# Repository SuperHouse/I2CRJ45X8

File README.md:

I2C to RJ45 Breakout (8 Port)
=============================
Copyright 2019-2021 SuperHouse Automation Pty Ltd  www.superhouse.tv  

8 RJ45 sockets connected to 32 I/O channels via I2C addressable
I/O controllers. Intended for use in building a home automation light
switch controller for connection to SuperHouse light switches.

Features:

 * 8 x RJ45 sockets for connection to light switches over Cat-5
 * I2C interface with interrupt output

This project has different versions:

 * 8-port version: https://github.com/superhouse/i2crj45x8
 * 16-port version: https://github.com/superhouse/i2crj45x16
 * 24-port version: https://github.com/superhouse/i2crj45x24
 * 24-port version with passthrough: https://github.com/superhouse/i2crj45x24pt

More information:

  http://www.superhouse.tv/i2crj45x8

INSTALLATION
------------
The design is saved as an EAGLE project. EAGLE PCB design software is
available from www.cadsoftusa.com free for non-commercial use. To use
this project download it and place the directory containing these files
into the "eagle" directory on your computer. Then open EAGLE and
navigate to the project.

CREDITS
-------
Designed by Jonathan Oxer jon@oxer.com.au

DISTRIBUTION
------------
The specific terms of distribution of this project are governed by the
license referenced below.

LICENSE
-------
Licensed under the TAPR Open Hardware License (www.tapr.org/OHL).
The "license" folder within this repository also contains a copy of
this license in plain text format.

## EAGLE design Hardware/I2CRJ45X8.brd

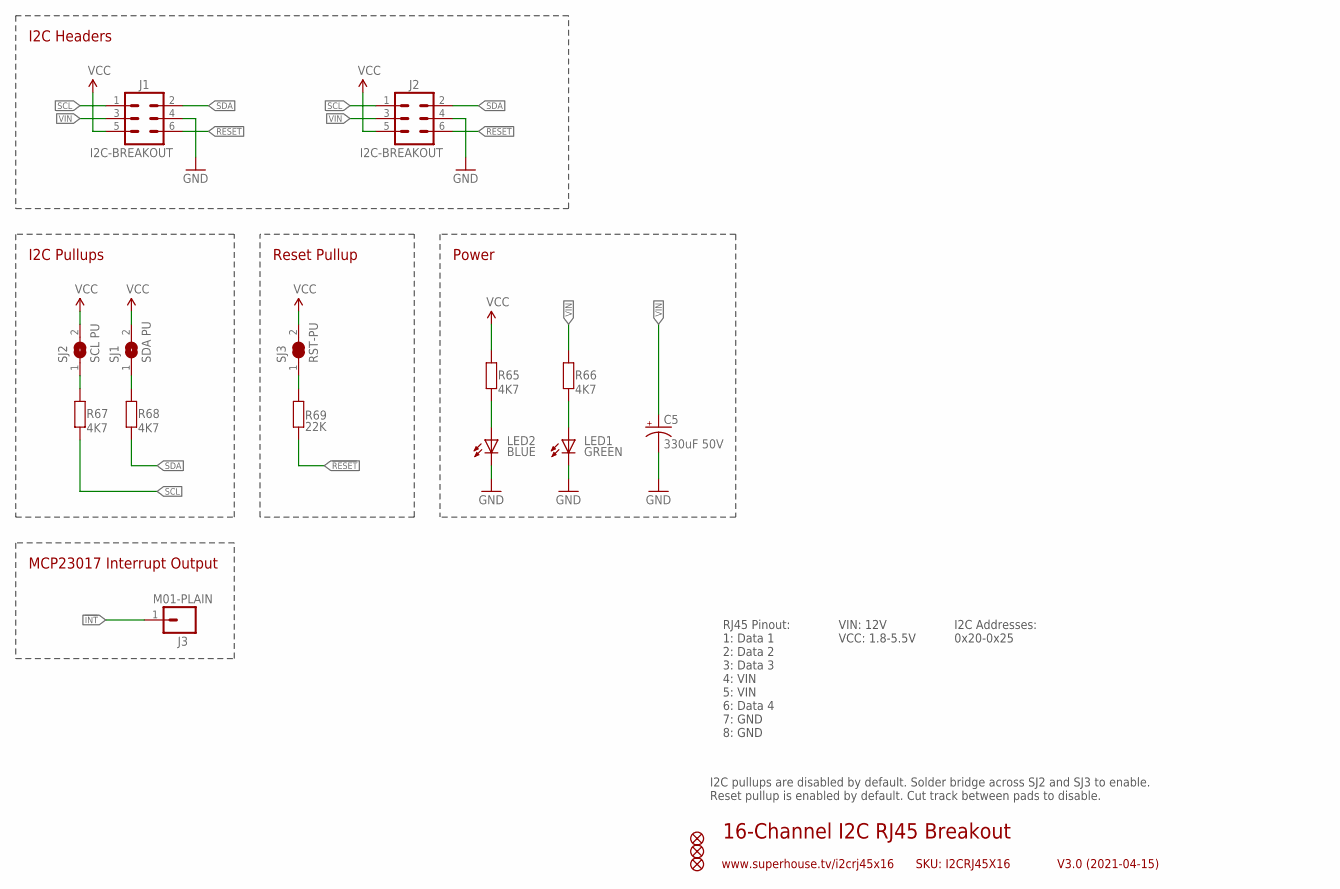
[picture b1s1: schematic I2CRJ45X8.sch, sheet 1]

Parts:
C5: 330uF 50V; PANASONIC_G
FID1, FID2, FID3: FIDUCIAL1X2.5; FIDUCIAL-1X2.5
J1, J2: I2C-BREAKOUT; 2X03-SHROUDED
J3: M01-PLAIN; 1X01
LED1: GREEN; LED-0603
LED2: BLUE; LED-0603
R65, R66, R67, R68: 4K7; R0603
R69: 22K; R0603
SJ1: SDA PU; SJ
SJ2: SCL PU; SJ
SJ3: RST-PU; SJC

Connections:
!INT: J3.1; also elsewhere on the board
!RESET: J1.6, J2.6, R69.1; also elsewhere on the board
GND: C5.-, J1.4, J2.4, LED1.C, LED2.C; also elsewhere on the board
unnamed: R67.2, SJ2.1
unnamed: R68.2, SJ1.1
unnamed: R69.2, SJ3.1
unnamed: LED2.A, R65.1
unnamed: LED1.A, R66.1
SCL: J1.1, J2.1, R67.1; also elsewhere on the board
SDA: J1.2, J2.2, R68.1; also elsewhere on the board
VCC: J1.5, J2.5, R65.2, SJ1.2, SJ2.2, SJ3.2; also elsewhere on the board
VIN: C5.+, J1.3, J2.3, R66.2; also elsewhere on the board

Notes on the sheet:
16-Channel I2C RJ45 Breakout
V3.0 (2021-04-15)
www.superhouse.tv/i2crj45x16
SKU: I2CRJ45X16
RJ45 Pinout: 1: Data 1 2: Data 2 3: Data 3 4: VIN 5: VIN 6: Data 4 7: GND 8: GND
VIN: 12V VCC: 1.8-5.5V
I2C Addresses: 0x20-0x25
I2C Headers
MCP23017 Interrupt Output
I2C Pullups
I2C pullups are disabled by default. Solder bridge across SJ2 and SJ3 to enable. Reset pullup is enabled by default. Cut track between pads to disable.
Power
Reset Pullup

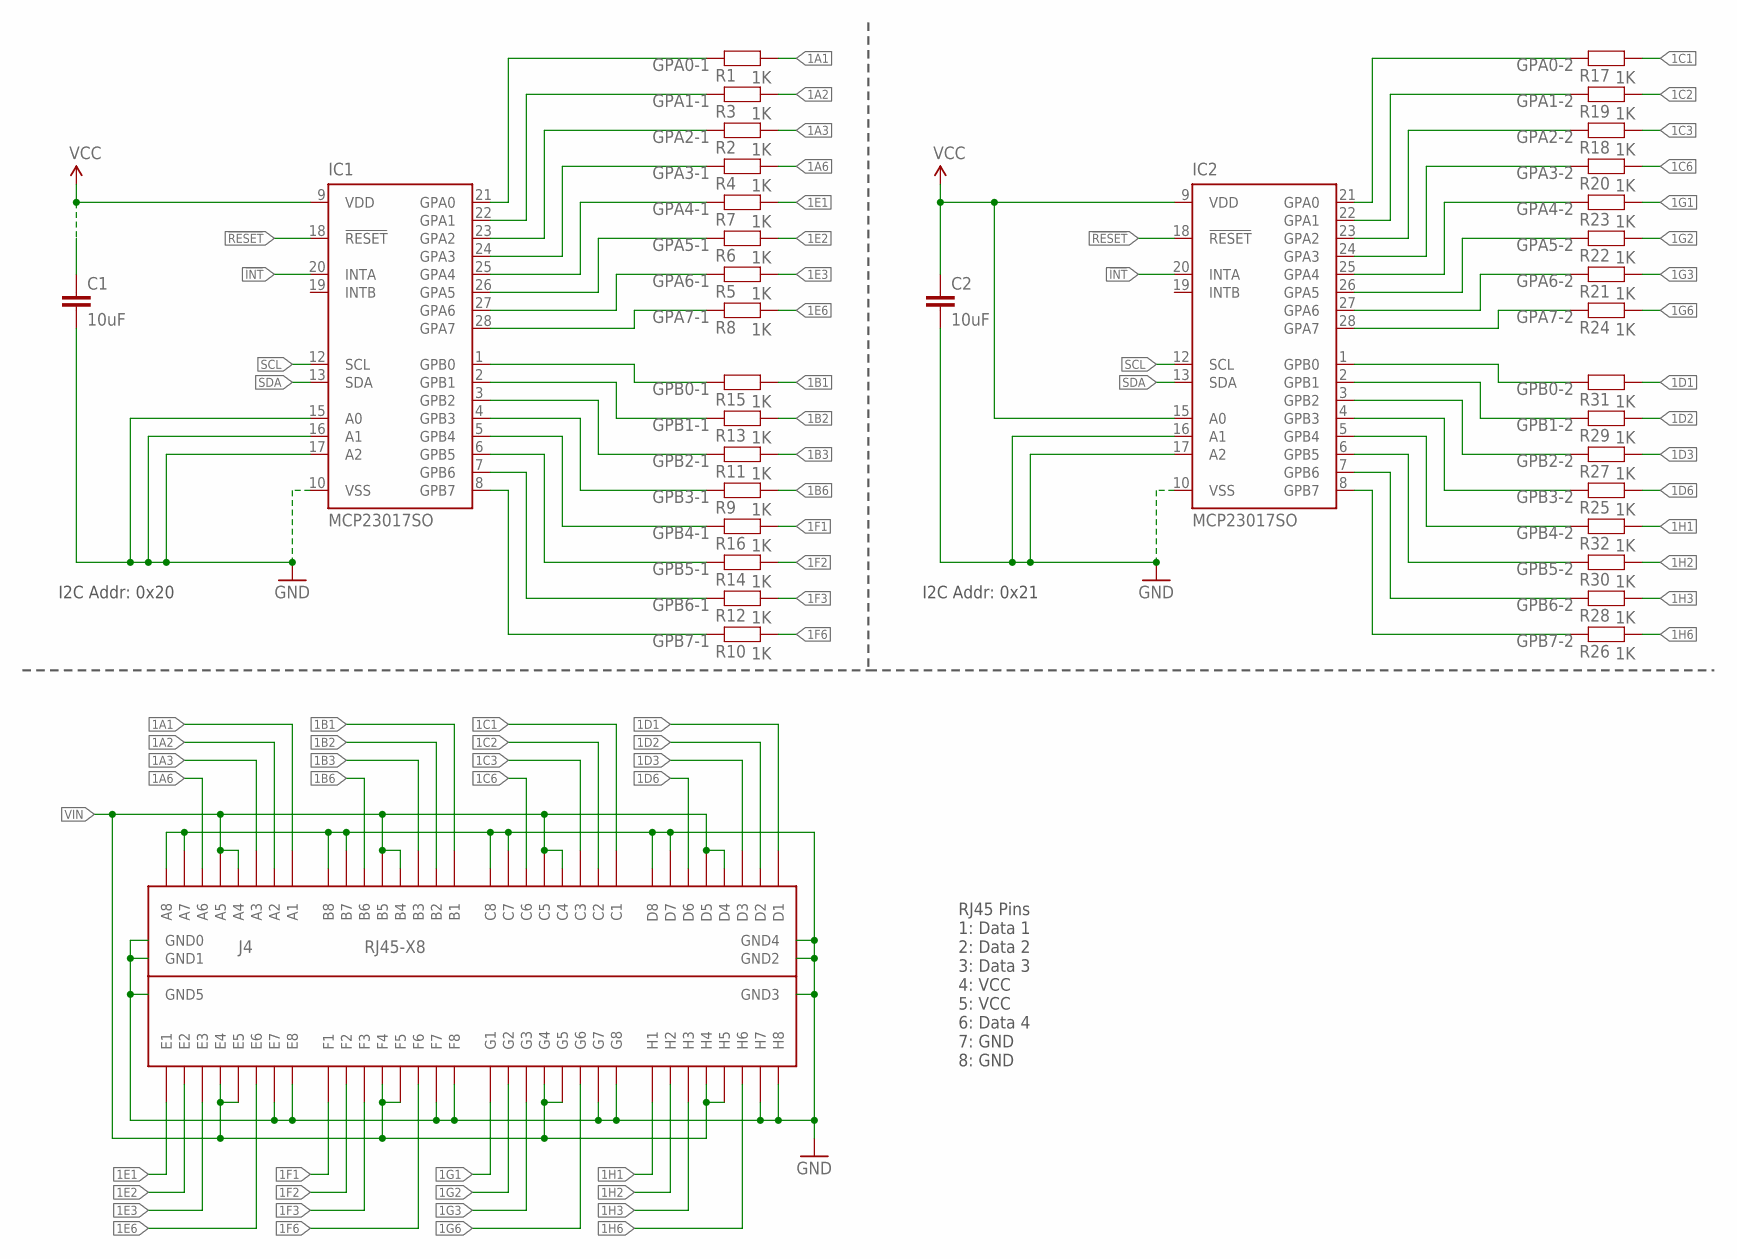
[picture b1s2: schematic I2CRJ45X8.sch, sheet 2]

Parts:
C1, C2: 10uF; C0805
IC1, IC2: MCP23017SO; SO28W
J4: RJ45-X8; RJ45-2X4
R1, R2, R3, R4, R5, R6, R7, R8, R9, R10, R11, R12, R13, R14, R15, R16, R17, R18, R19, R20, R21, R22, R23, R24, R25, R26, R27, R28, R29, R30, R31, R32: 1K; R0603

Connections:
1A1: J4.A1, R1.2
1A2: J4.A2, R3.2
1A3: J4.A3, R2.2
1A6: J4.A6, R4.2
1B1: J4.B1, R15.2
1B2: J4.B2, R13.2
1B3: J4.B3, R11.2
1B6: J4.B6, R9.2
1C1: J4.C1, R17.2
1C2: J4.C2, R19.2
1C3: J4.C3, R18.2
1C6: J4.C6, R20.2
1D1: J4.D1, R31.2
1D2: J4.D2, R29.2
1D3: J4.D3, R27.2
1D6: J4.D6, R25.2
1E1: J4.E1, R7.2
1E2: J4.E2, R6.2
1E3: J4.E3, R5.2
1E6: J4.E6, R8.2
1F1: J4.F1, R16.2
1F2: J4.F2, R14.2
1F3: J4.F3, R12.2
1F6: J4.F6, R10.2
1G1: J4.G1, R23.2
1G2: J4.G2, R22.2
1G3: J4.G3, R21.2
1G6: J4.G6, R24.2
1H1: J4.H1, R32.2
1H2: J4.H2, R30.2
1H3: J4.H3, R28.2
1H6: J4.H6, R26.2
!INT: IC1.20 (INTA), IC2.20 (INTA); also elsewhere on the board
!RESET: IC1.18 (!RESET), IC2.18 (!RESET); also elsewhere on the board
GND: C1.2, C2.2, IC1.10 (VSS), IC1.15 (A0), IC1.16 (A1), IC1.17 (A2), IC2.10 (VSS), IC2.16 (A1), IC2.17 (A2), J4.A7, J4.A8, J4.B7, J4.B8, J4.C7, J4.C8, J4.D7, J4.D8, J4.E7, J4.E8, J4.F7, J4.F8, J4.G7, J4.G8, J4.GND0, J4.GND1, J4.GND2, J4.GND3, J4.GND4, J4.GND5, J4.H7, J4.H8; also elsewhere on the board
GPA0-1: IC1.21 (GPA0), R1.1
GPA0-2: IC2.21 (GPA0), R17.1
GPA1-1: IC1.22 (GPA1), R3.1
GPA1-2: IC2.22 (GPA1), R19.1
GPA2-1: IC1.23 (GPA2), R2.1
GPA2-2: IC2.23 (GPA2), R18.1
GPA3-1: IC1.24 (GPA3), R4.1
GPA3-2: IC2.24 (GPA3), R20.1
GPA4-1: IC1.25 (GPA4), R7.1
GPA4-2: IC2.25 (GPA4), R23.1
GPA5-1: IC1.26 (GPA5), R6.1
GPA5-2: IC2.26 (GPA5), R22.1
GPA6-1: IC1.27 (GPA6), R5.1
GPA6-2: IC2.27 (GPA6), R21.1
GPA7-1: IC1.28 (GPA7), R8.1
GPA7-2: IC2.28 (GPA7), R24.1
GPB0-1: IC1.1 (GPB0), R15.1
GPB0-2: IC2.1 (GPB0), R31.1
GPB1-1: IC1.2 (GPB1), R13.1
GPB1-2: IC2.2 (GPB1), R29.1
GPB2-1: IC1.3 (GPB2), R11.1
GPB2-2: IC2.3 (GPB2), R27.1
GPB3-1: IC1.4 (GPB3), R9.1
GPB3-2: IC2.4 (GPB3), R25.1
GPB4-1: IC1.5 (GPB4), R16.1
GPB4-2: IC2.5 (GPB4), R32.1
GPB5-1: IC1.6 (GPB5), R14.1
GPB5-2: IC2.6 (GPB5), R30.1
GPB6-1: IC1.7 (GPB6), R12.1
GPB6-2: IC2.7 (GPB6), R28.1
GPB7-1: IC1.8 (GPB7), R10.1
GPB7-2: IC2.8 (GPB7), R26.1
SCL: IC1.12 (SCL), IC2.12 (SCL); also elsewhere on the board
SDA: IC1.13 (SDA), IC2.13 (SDA); also elsewhere on the board
VCC: C1.1, C2.1, IC1.9 (VDD), IC2.9 (VDD), IC2.15 (A0); also elsewhere on the board
VIN: J4.A4, J4.A5, J4.B4, J4.B5, J4.C4, J4.C5, J4.D4, J4.D5, J4.E4, J4.E5, J4.F4, J4.F5, J4.G4, J4.G5, J4.H4, J4.H5; also elsewhere on the board

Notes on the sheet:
RJ45 Pins 1: Data 1 2: Data 2 3: Data 3 4: VCC 5: VCC 6: Data 4 7: GND 8: GND
I2C Addr: 0x20
I2C Addr: 0x21

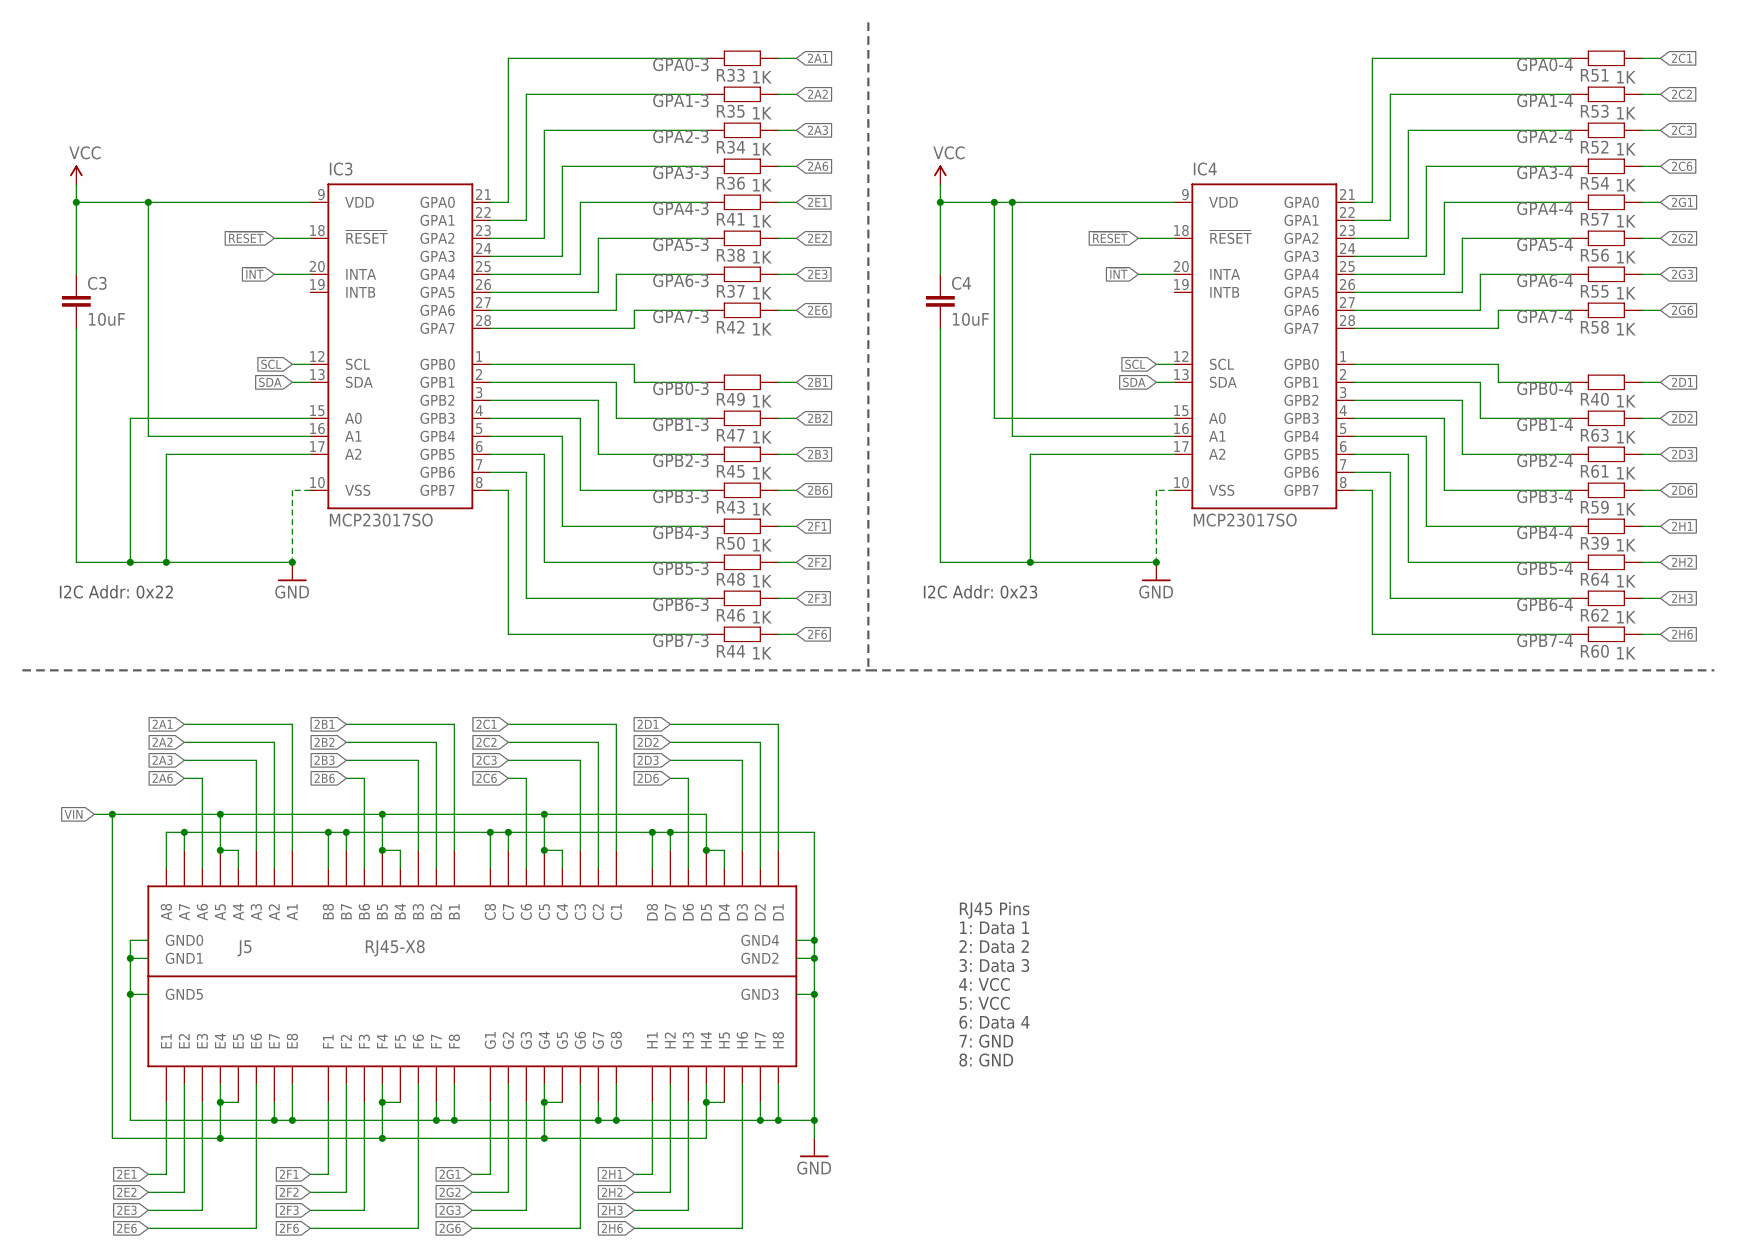
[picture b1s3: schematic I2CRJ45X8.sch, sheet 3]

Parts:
C3, C4: 10uF; C0805
IC3, IC4: MCP23017SO; SO28W
J5: RJ45-X8; RJ45-2X4
R33, R34, R35, R36, R37, R38, R39, R40, R41, R42, R43, R44, R45, R46, R47, R48, R49, R50, R51, R52, R53, R54, R55, R56, R57, R58, R59, R60, R61, R62, R63, R64: 1K; R0603

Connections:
2A1: J5.A1, R33.2
2A2: J5.A2, R35.2
2A3: J5.A3, R34.2
2A6: J5.A6, R36.2
2B1: J5.B1, R49.2
2B2: J5.B2, R47.2
2B3: J5.B3, R45.2
2B6: J5.B6, R43.2
2C1: J5.C1, R51.2
2C2: J5.C2, R53.2
2C3: J5.C3, R52.2
2C6: J5.C6, R54.2
2D1: J5.D1, R40.2
2D2: J5.D2, R63.2
2D3: J5.D3, R61.2
2D6: J5.D6, R59.2
2E1: J5.E1, R41.2
2E2: J5.E2, R38.2
2E3: J5.E3, R37.2
2E6: J5.E6, R42.2
2F1: J5.F1, R50.2
2F2: J5.F2, R48.2
2F3: J5.F3, R46.2
2F6: J5.F6, R44.2
2G1: J5.G1, R57.2
2G2: J5.G2, R56.2
2G3: J5.G3, R55.2
2G6: J5.G6, R58.2
2H1: J5.H1, R39.2
2H2: J5.H2, R64.2
2H3: J5.H3, R62.2
2H6: J5.H6, R60.2
!INT: IC3.20 (INTA), IC4.20 (INTA); also elsewhere on the board
!RESET: IC3.18 (!RESET), IC4.18 (!RESET); also elsewhere on the board
GND: C3.2, C4.2, IC3.10 (VSS), IC3.15 (A0), IC3.17 (A2), IC4.10 (VSS), IC4.17 (A2), J5.A7, J5.A8, J5.B7, J5.B8, J5.C7, J5.C8, J5.D7, J5.D8, J5.E7, J5.E8, J5.F7, J5.F8, J5.G7, J5.G8, J5.GND0, J5.GND1, J5.GND2, J5.GND3, J5.GND4, J5.GND5, J5.H7, J5.H8; also elsewhere on the board
GPA0-3: IC3.21 (GPA0), R33.1
GPA0-4: IC4.21 (GPA0), R51.1
GPA1-3: IC3.22 (GPA1), R35.1
GPA1-4: IC4.22 (GPA1), R53.1
GPA2-3: IC3.23 (GPA2), R34.1
GPA2-4: IC4.23 (GPA2), R52.1
GPA3-3: IC3.24 (GPA3), R36.1
GPA3-4: IC4.24 (GPA3), R54.1
GPA4-3: IC3.25 (GPA4), R41.1
GPA4-4: IC4.25 (GPA4), R57.1
GPA5-3: IC3.26 (GPA5), R38.1
GPA5-4: IC4.26 (GPA5), R56.1
GPA6-3: IC3.27 (GPA6), R37.1
GPA6-4: IC4.27 (GPA6), R55.1
GPA7-3: IC3.28 (GPA7), R42.1
GPA7-4: IC4.28 (GPA7), R58.1
GPB0-3: IC3.1 (GPB0), R49.1
GPB0-4: IC4.1 (GPB0), R40.1
GPB1-3: IC3.2 (GPB1), R47.1
GPB1-4: IC4.2 (GPB1), R63.1
GPB2-3: IC3.3 (GPB2), R45.1
GPB2-4: IC4.3 (GPB2), R61.1
GPB3-3: IC3.4 (GPB3), R43.1
GPB3-4: IC4.4 (GPB3), R59.1
GPB4-3: IC3.5 (GPB4), R50.1
GPB4-4: IC4.5 (GPB4), R39.1
GPB5-3: IC3.6 (GPB5), R48.1
GPB5-4: IC4.6 (GPB5), R64.1
GPB6-3: IC3.7 (GPB6), R46.1
GPB6-4: IC4.7 (GPB6), R62.1
GPB7-3: IC3.8 (GPB7), R44.1
GPB7-4: IC4.8 (GPB7), R60.1
SCL: IC3.12 (SCL), IC4.12 (SCL); also elsewhere on the board
SDA: IC3.13 (SDA), IC4.13 (SDA); also elsewhere on the board
VCC: C3.1, C4.1, IC3.9 (VDD), IC3.16 (A1), IC4.9 (VDD), IC4.15 (A0), IC4.16 (A1); also elsewhere on the board
VIN: J5.A4, J5.A5, J5.B4, J5.B5, J5.C4, J5.C5, J5.D4, J5.D5, J5.E4, J5.E5, J5.F4, J5.F5, J5.G4, J5.G5, J5.H4, J5.H5; also elsewhere on the board

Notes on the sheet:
RJ45 Pins 1: Data 1 2: Data 2 3: Data 3 4: VCC 5: VCC 6: Data 4 7: GND 8: GND
I2C Addr: 0x22
I2C Addr: 0x23

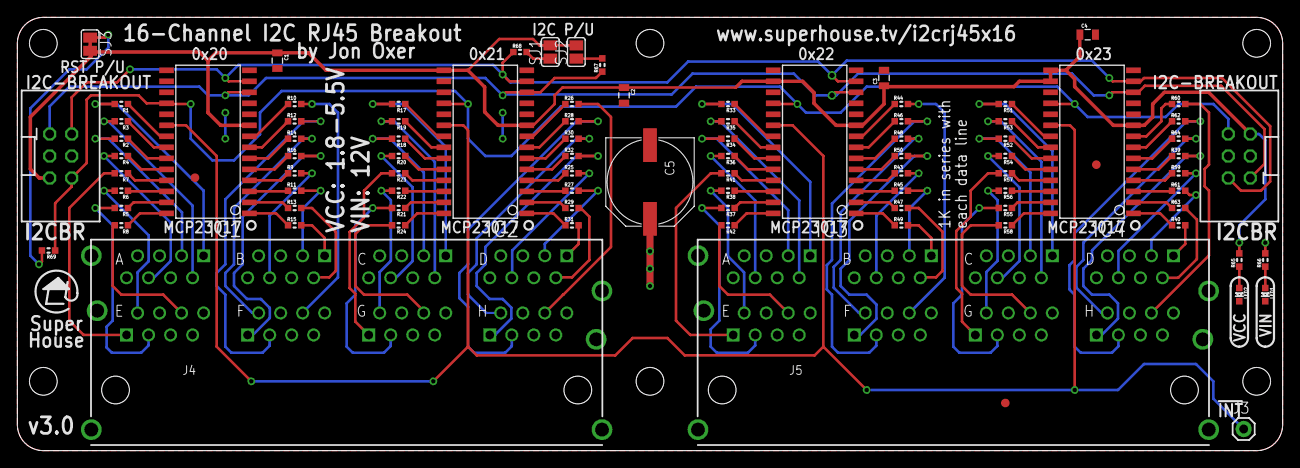
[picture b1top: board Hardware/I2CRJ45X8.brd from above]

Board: 2 copper layers, 146.0 x 50.0 mm, 91 parts (0 on the bottom side), 140 nets.

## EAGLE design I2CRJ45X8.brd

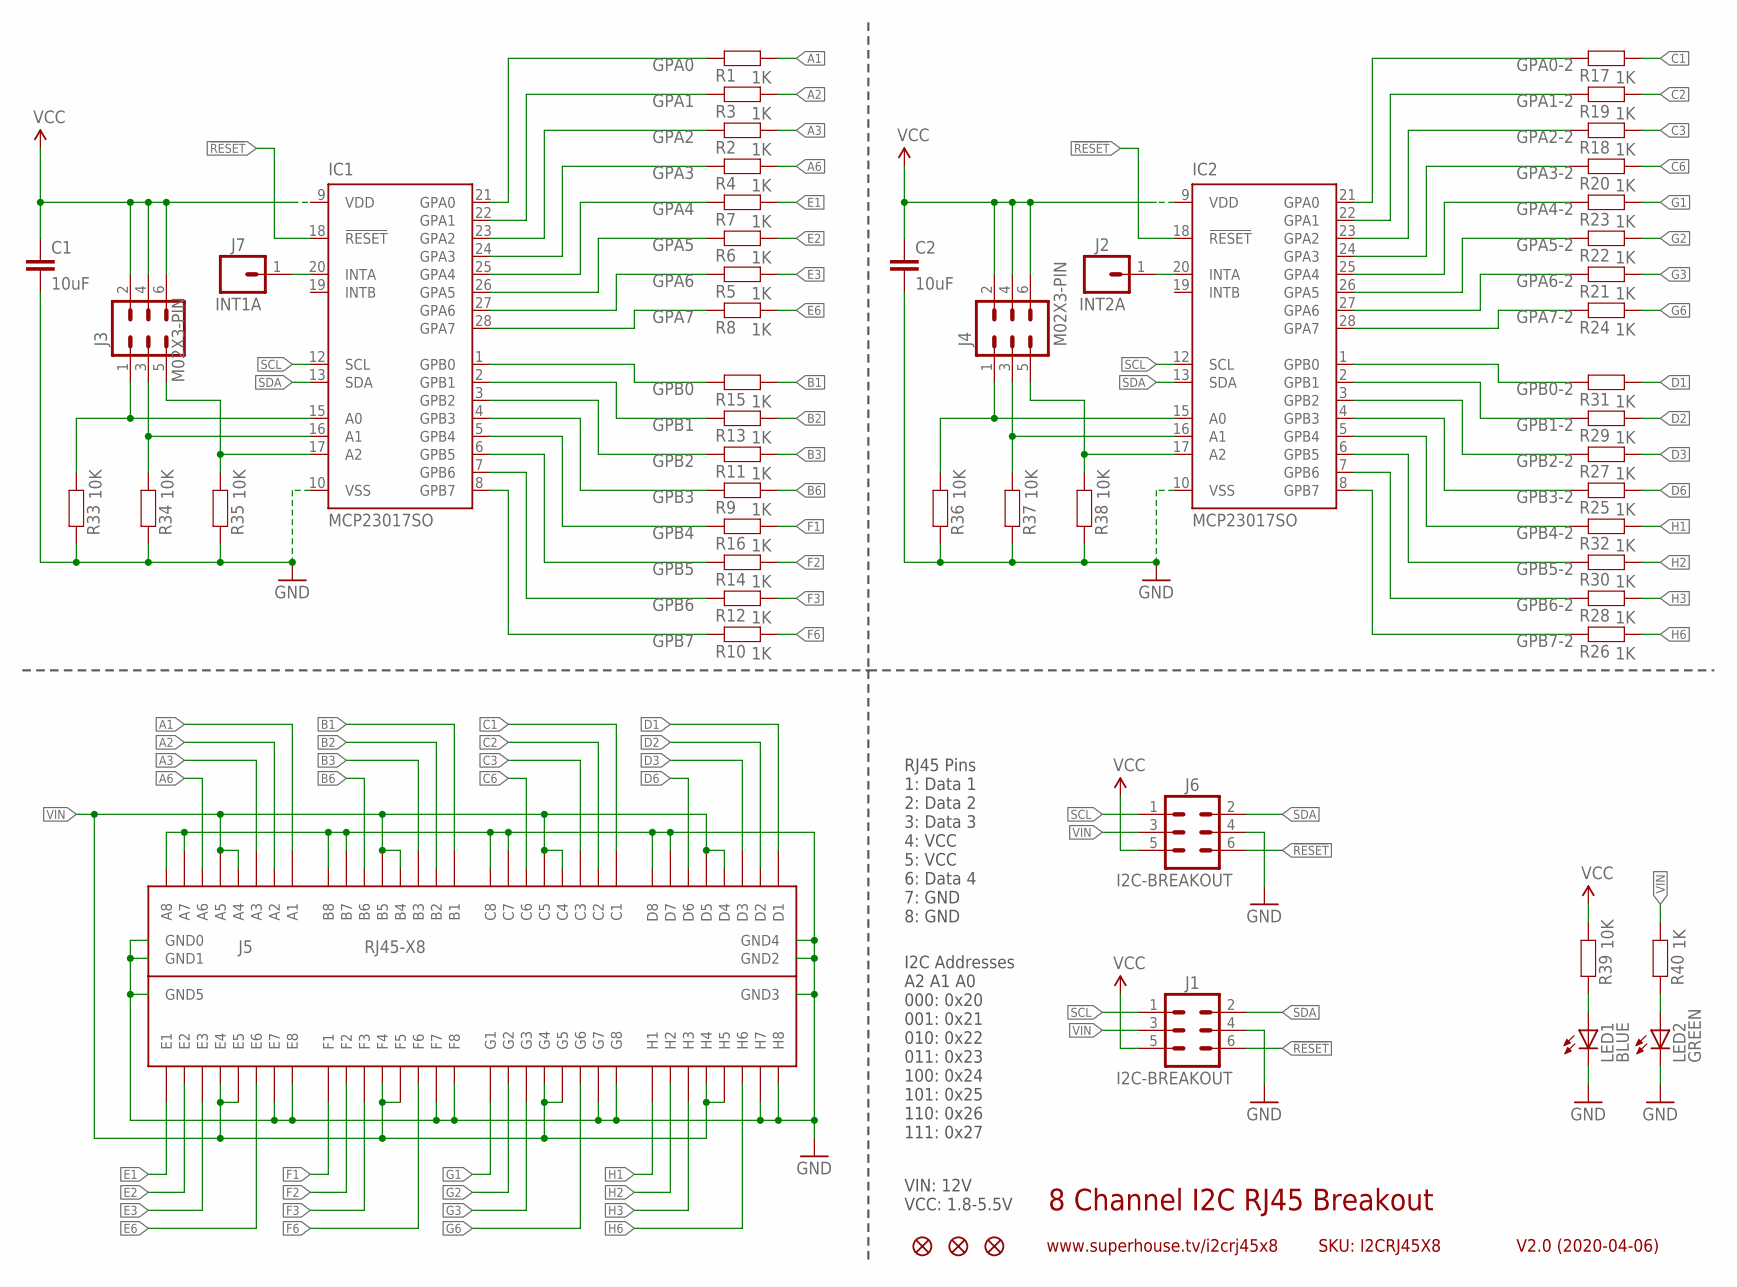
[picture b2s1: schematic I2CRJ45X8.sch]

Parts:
C1, C2: 10uF; C0805
FID1, FID2, FID3: FIDUCIAL1X2.5; FIDUCIAL-1X2.5
IC1, IC2: MCP23017SO; SO28W
J1, J6: I2C-BREAKOUT; 2X03-SHROUDED
J2: INT2A; 1X01
J3, J4: M02X3-PIN; 2X03-P
J5: RJ45-X8; RJ45-2X4
J7: INT1A; 1X01
LED1: BLUE; LED-0603
LED2: GREEN; LED-0603
R1, R2, R3, R4, R5, R6, R7, R8, R9, R10, R11, R12, R13, R14, R15, R16, R17, R18, R19, R20, R21, R22, R23, R24, R25, R26, R27, R28, R29, R30, R31, R32, R40: 1K; R0603
R33, R34, R35, R36, R37, R38, R39: 10K; R0603

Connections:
!RESET: IC1.18 (!RESET), IC2.18 (!RESET), J1.6, J6.6
A1: J5.A1, R1.2
A2: J5.A2, R3.2
A3: J5.A3, R2.2
A6: J5.A6, R4.2
B1: J5.B1, R15.2
B2: J5.B2, R13.2
B3: J5.B3, R11.2
B6: J5.B6, R9.2
C1: J5.C1, R17.2
C2: J5.C2, R19.2
C3: J5.C3, R18.2
C6: J5.C6, R20.2
D1: J5.D1, R31.2
D2: J5.D2, R29.2
D3: J5.D3, R27.2
D6: J5.D6, R25.2
E1: J5.E1, R7.2
E2: J5.E2, R6.2
E3: J5.E3, R5.2
E6: J5.E6, R8.2
F1: J5.F1, R16.2
F2: J5.F2, R14.2
F3: J5.F3, R12.2
F6: J5.F6, R10.2
G1: J5.G1, R23.2
G2: J5.G2, R22.2
G3: J5.G3, R21.2
G6: J5.G6, R24.2
GND: C1.2, C2.2, IC1.10 (VSS), IC2.10 (VSS), J1.4, J5.A7, J5.A8, J5.B7, J5.B8, J5.C7, J5.C8, J5.D7, J5.D8, J5.E7, J5.E8, J5.F7, J5.F8, J5.G7, J5.G8, J5.GND0, J5.GND1, J5.GND2, J5.GND3, J5.GND4, J5.GND5, J5.H7, J5.H8, J6.4, LED1.C, LED2.C, R33.1, R34.1, R35.1, R36.1, R37.1, R38.1
GPA0: IC1.21 (GPA0), R1.1
GPA0-2: IC2.21 (GPA0), R17.1
GPA1: IC1.22 (GPA1), R3.1
GPA1-2: IC2.22 (GPA1), R19.1
GPA2: IC1.23 (GPA2), R2.1
GPA2-2: IC2.23 (GPA2), R18.1
GPA3: IC1.24 (GPA3), R4.1
GPA3-2: IC2.24 (GPA3), R20.1
GPA4: IC1.25 (GPA4), R7.1
GPA4-2: IC2.25 (GPA4), R23.1
GPA5: IC1.26 (GPA5), R6.1
GPA5-2: IC2.26 (GPA5), R22.1
GPA6: IC1.27 (GPA6), R5.1
GPA6-2: IC2.27 (GPA6), R21.1
GPA7: IC1.28 (GPA7), R8.1
GPA7-2: IC2.28 (GPA7), R24.1
GPB0: IC1.1 (GPB0), R15.1
GPB0-2: IC2.1 (GPB0), R31.1
GPB1: IC1.2 (GPB1), R13.1
GPB1-2: IC2.2 (GPB1), R29.1
GPB2: IC1.3 (GPB2), R11.1
GPB2-2: IC2.3 (GPB2), R27.1
GPB3: IC1.4 (GPB3), R9.1
GPB3-2: IC2.4 (GPB3), R25.1
GPB4: IC1.5 (GPB4), R16.1
GPB4-2: IC2.5 (GPB4), R32.1
GPB5: IC1.6 (GPB5), R14.1
GPB5-2: IC2.6 (GPB5), R30.1
GPB6: IC1.7 (GPB6), R12.1
GPB6-2: IC2.7 (GPB6), R28.1
GPB7: IC1.8 (GPB7), R10.1
GPB7-2: IC2.8 (GPB7), R26.1
H1: J5.H1, R32.2
H2: J5.H2, R30.2
H3: J5.H3, R28.2
H6: J5.H6, R26.2
unnamed: IC2.16 (A1), J4.3, R37.2
unnamed: IC1.17 (A2), J3.5, R35.2
unnamed: IC1.16 (A1), J3.3, R34.2
unnamed: IC1.15 (A0), J3.1, R33.2
unnamed: IC2.15 (A0), J4.1, R36.2
unnamed: IC2.17 (A2), J4.5, R38.2
unnamed: LED1.A, R39.1
unnamed: LED2.A, R40.1
unnamed: IC2.20 (INTA), J2.1
unnamed: IC1.20 (INTA), J7.1
SCL: IC1.12 (SCL), IC2.12 (SCL), J1.1, J6.1
SDA: IC1.13 (SDA), IC2.13 (SDA), J1.2, J6.2
VCC: C1.1, C2.1, IC1.9 (VDD), IC2.9 (VDD), J1.5, J3.2, J3.4, J3.6, J4.2, J4.4, J4.6, J6.5, R39.2
VIN: J1.3, J5.A4, J5.A5, J5.B4, J5.B5, J5.C4, J5.C5, J5.D4, J5.D5, J5.E4, J5.E5, J5.F4, J5.F5, J5.G4, J5.G5, J5.H4, J5.H5, J6.3, R40.2

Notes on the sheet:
RJ45 Pins 1: Data 1 2: Data 2 3: Data 3 4: VCC 5: VCC 6: Data 4 7: GND 8: GND
8 Channel I2C RJ45 Breakout
V2.0 (2020-04-06)
www.superhouse.tv/i2crj45x8
SKU: I2CRJ45X8
I2C Addresses A2 A1 A0 000: 0x20 001: 0x21 010: 0x22 011: 0x23 100: 0x24 101: 0x25 110: 0x26 111: 0x27
VIN: 12V VCC: 1.8-5.5V

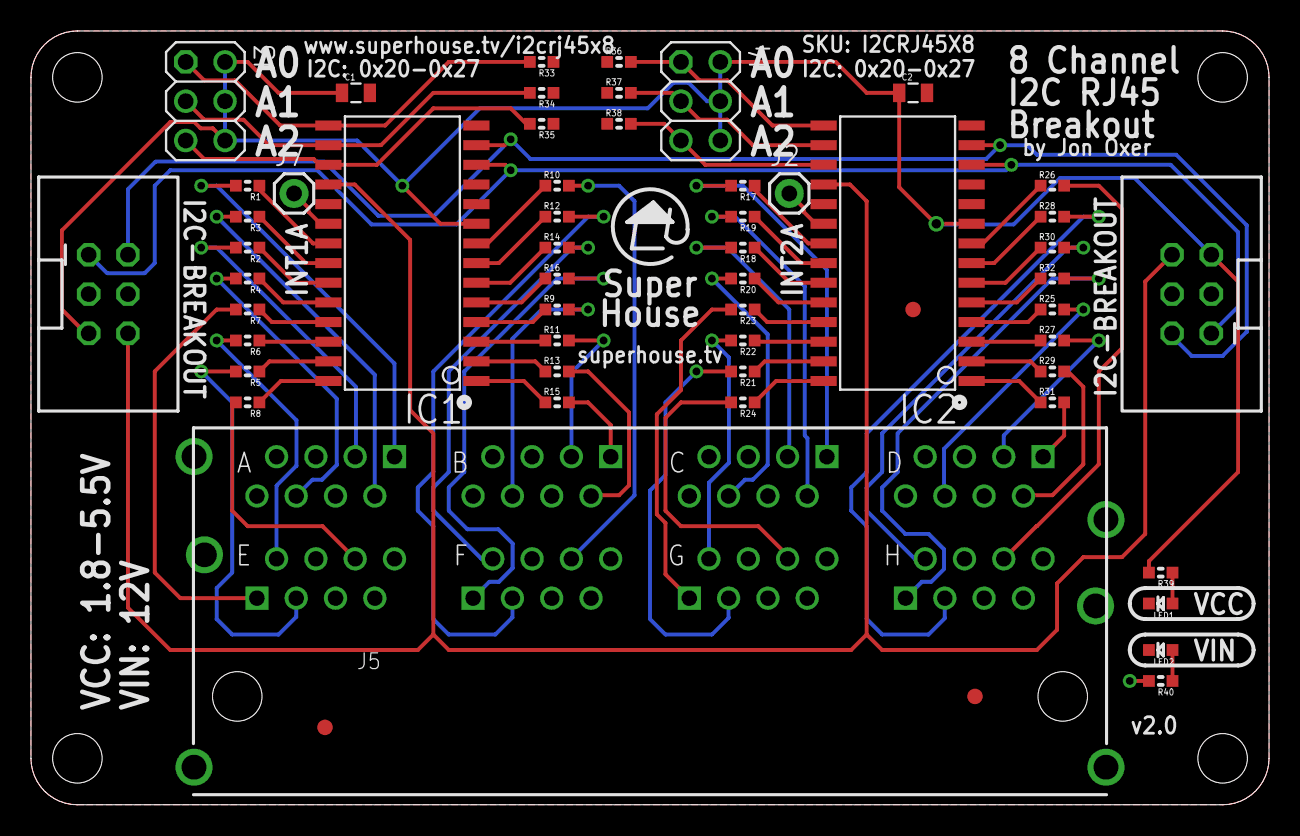
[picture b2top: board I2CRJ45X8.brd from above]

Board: 2 copper layers, 80.0 x 50.0 mm, 56 parts (0 on the bottom side), 80 nets.

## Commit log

2019-09-07 Renamed project files for consistency with related projects
2019-09-07 Board and schematic labelling
2019-09-07 Routing, Silkscreen Updated
    Routed VIN, changed silkscreen for VCC and VIN LEDS to match corrent circuit
2019-09-07 Part updates
2019-09-07 Added fiducials
2019-09-13 Switched fiducials to SuperHouse library
2019-09-20 Start of conversion to I2C Breakout header (2x3 shrouded)
2019-09-20 Routing for I2C Breakout headers
2019-09-21 Experimenting with options for linking MCP reset to I2C Breakout reset
2019-10-03 Routing for 2x3 I2C Breakout header
2020-04-08 Converted to I2C-BREAKOUT header for v2.0 release
2021-04-12 Moved hardware files into subdirectory.
2021-04-12 Reduced width of PCB. Adjusted mounting hole locations. Improved GND connections. Changed position of power LEDs.
2021-04-13 Silkscreen, clearances, and DRC for v2.2 release.
2021-04-13 Added I2C pullups and silkscreen improvements.
2021-04-13 Added v2.2 render.
2021-04-13 Embedded image in README.
2021-04-13 Added IC part number to silkscreen.
2021-04-15 Renamed existing project files.
2021-04-15 Moved in files from x16 version to begin conversion.
2021-04-15 Major update based on 24-port project. Use solder jumpers for I2C address selection.
2021-04-15 Added v3.0 render.
2021-04-15 Updated embedded image and added links to versions.
2021-04-15 Added link to 24-port version with passthrough.

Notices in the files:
I2CRJ45X8.brd:
(C)2019-2020 SuperHouse Automation Pty Ltd
Released under the terms of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
